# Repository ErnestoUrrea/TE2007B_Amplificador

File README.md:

# Amplificador de señales analógico con BJT
Circuito de amplificación de señales analógico de 3 etapas basado en transistores de unión bipolar y componentes pasivos. Diseñado para la unidad de formacion TE2007B.

**Equipo:** <br>
César Aurelio Martínez Rodríguez<br>
Mario Alberto Sánchez López<br>
Ernesto Enrique Urrea López<br>

## Especificaciones

El circuito se diseñó para cumplir con las siguientes especificaciones:
- Uso de BJT y componentes pasivos unicamente.
- Alimentación de +-12 VDC.
- Etapa de salida seguidor-emisor con arreglo Darlington.
- Entrada de audio de 60 mV pico.
- Salida de audio para alimentación de una bocina de 0.5 W, 8 Ω.

## Diagrama esquemático

## Vista 3D

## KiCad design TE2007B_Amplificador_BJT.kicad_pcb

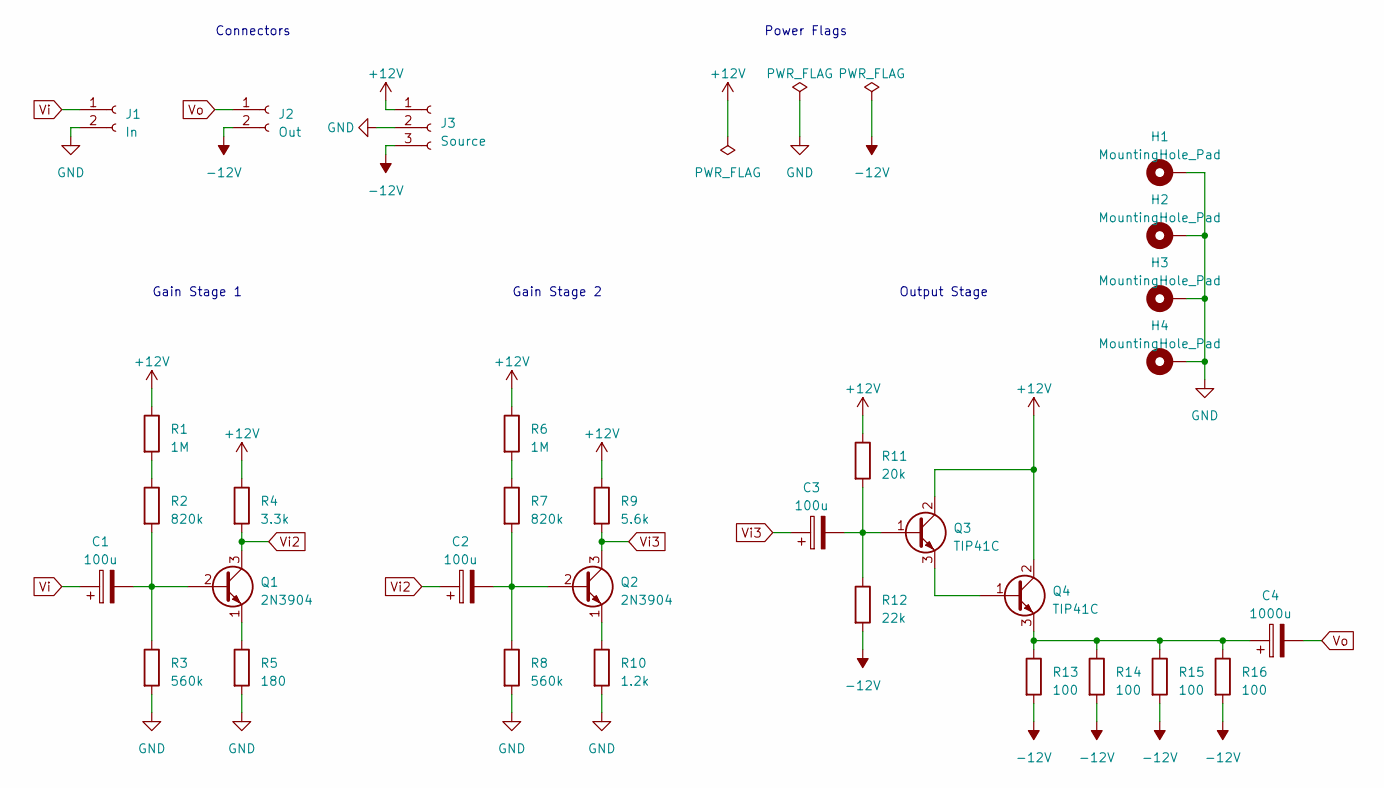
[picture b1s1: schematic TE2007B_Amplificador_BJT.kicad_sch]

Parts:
C1, C2, C3: 100u; CP_Radial_D8.0mm_P3.50mm
C4: 1000u; CP_Radial_D12.5mm_P5.00mm
H1, H2, H3, H4: MountingHole_Pad; MountingHole_2.5mm_Pad
J1: In; TerminalBlock_Phoenix_MKDS-1,5-2_1x02_P5.00mm_Horizontal
J2: Out; TerminalBlock_Phoenix_MKDS-1,5-2_1x02_P5.00mm_Horizontal
J3: Source; TerminalBlock_Phoenix_MKDS-1,5-3_1x03_P5.00mm_Horizontal
Q1, Q2: 2N3904; TO-92_Inline
Q3, Q4: TIP41C; TO-220-3_Vertical
R1, R6: 1M; R_Axial_DIN0411_L9.9mm_D3.6mm_P15.24mm_Horizontal
R2, R7: 820k; R_Axial_DIN0411_L9.9mm_D3.6mm_P15.24mm_Horizontal
R3, R8: 560k; R_Axial_DIN0411_L9.9mm_D3.6mm_P15.24mm_Horizontal
R4: 3.3k; R_Axial_DIN0411_L9.9mm_D3.6mm_P15.24mm_Horizontal
R5: 180; R_Axial_DIN0411_L9.9mm_D3.6mm_P15.24mm_Horizontal
R9: 5.6k; R_Axial_DIN0411_L9.9mm_D3.6mm_P15.24mm_Horizontal
R10: 1.2k; R_Axial_DIN0411_L9.9mm_D3.6mm_P15.24mm_Horizontal
R11: 20k; R_Axial_DIN0411_L9.9mm_D3.6mm_P15.24mm_Horizontal
R12: 22k; R_Axial_DIN0411_L9.9mm_D3.6mm_P15.24mm_Horizontal
R13, R14, R15, R16: 100; R_Axial_DIN0411_L9.9mm_D3.6mm_P15.24mm_Horizontal

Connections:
+12V: J3.1, Q3.2 (C), Q4.2 (C), R1.1, R4.1, R6.1, R9.1, R11.1
-12V: J2.2, J3.3, R12.2, R13.2, R14.2, R15.2, R16.2
GND: H1.1, H2.1, H3.1, H4.1, J1.2, J3.2, R3.2, R5.2, R8.2, R10.2
unnamed: C1.2, Q1.2 (B), R2.2, R3.1
unnamed: Q1.1 (E), R5.1
unnamed: C2.2, Q2.2 (B), R7.2, R8.1
unnamed: Q2.1 (E), R10.1
unnamed: C3.2, Q3.1 (B), R11.2, R12.1
unnamed: Q3.3 (E), Q4.1 (B)
unnamed: C4.1, Q4.3 (E), R13.1, R14.1, R15.1, R16.1
unnamed: R1.2, R2.1
unnamed: R6.2, R7.1
Vi: C1.1, J1.1
Vi2: C2.1, Q1.3 (C), R4.2
Vi3: C3.1, Q2.3 (C), R9.2
Vo: C4.2, J2.1

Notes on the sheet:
Connectors
Gain Stage 2
Gain Stage 1
Output Stage
Power Flags

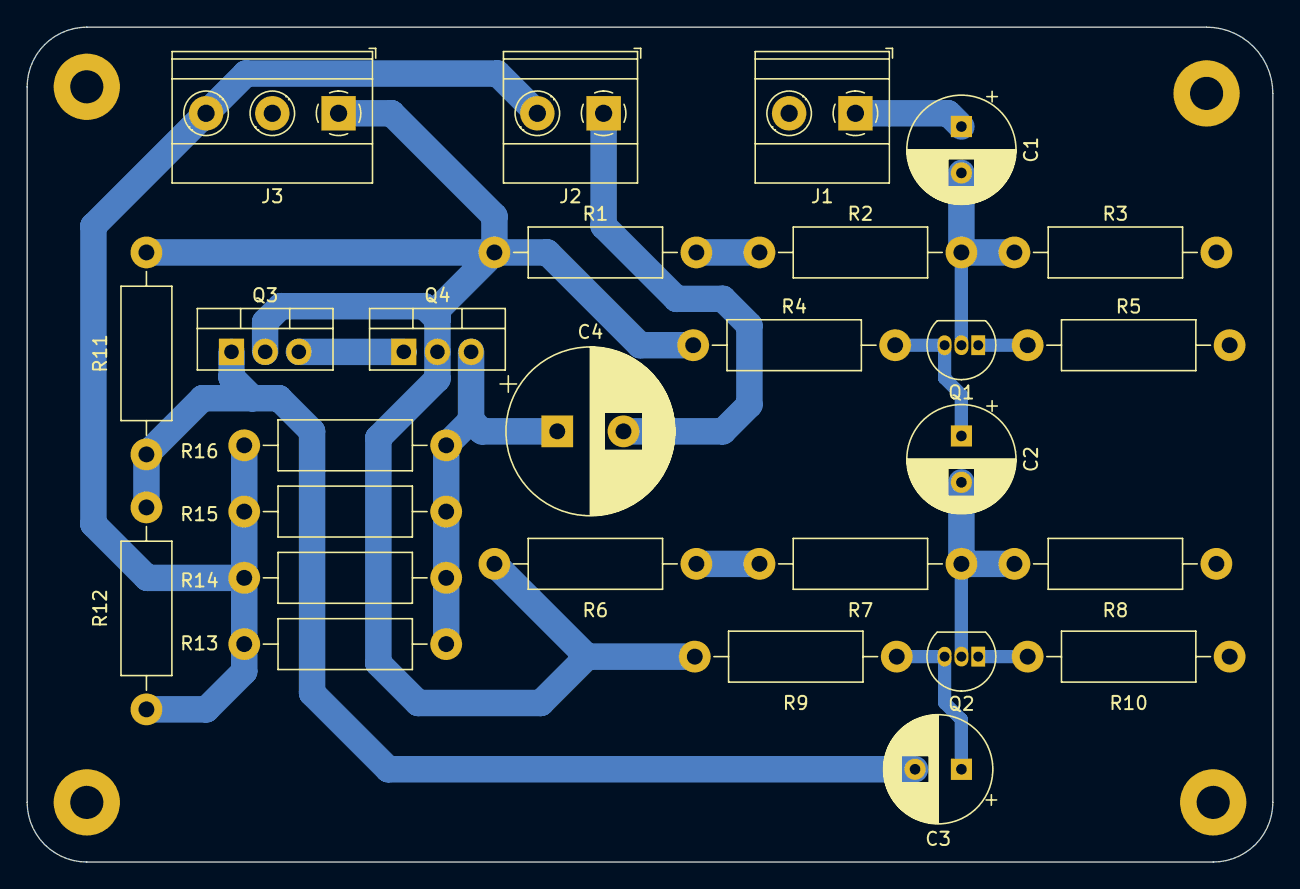
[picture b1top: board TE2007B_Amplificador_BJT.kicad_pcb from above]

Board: 2 copper layers, 94.0 x 63.0 mm, 31 parts (0 on the bottom side), 16 nets.

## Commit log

2023-07-18 3D view image
